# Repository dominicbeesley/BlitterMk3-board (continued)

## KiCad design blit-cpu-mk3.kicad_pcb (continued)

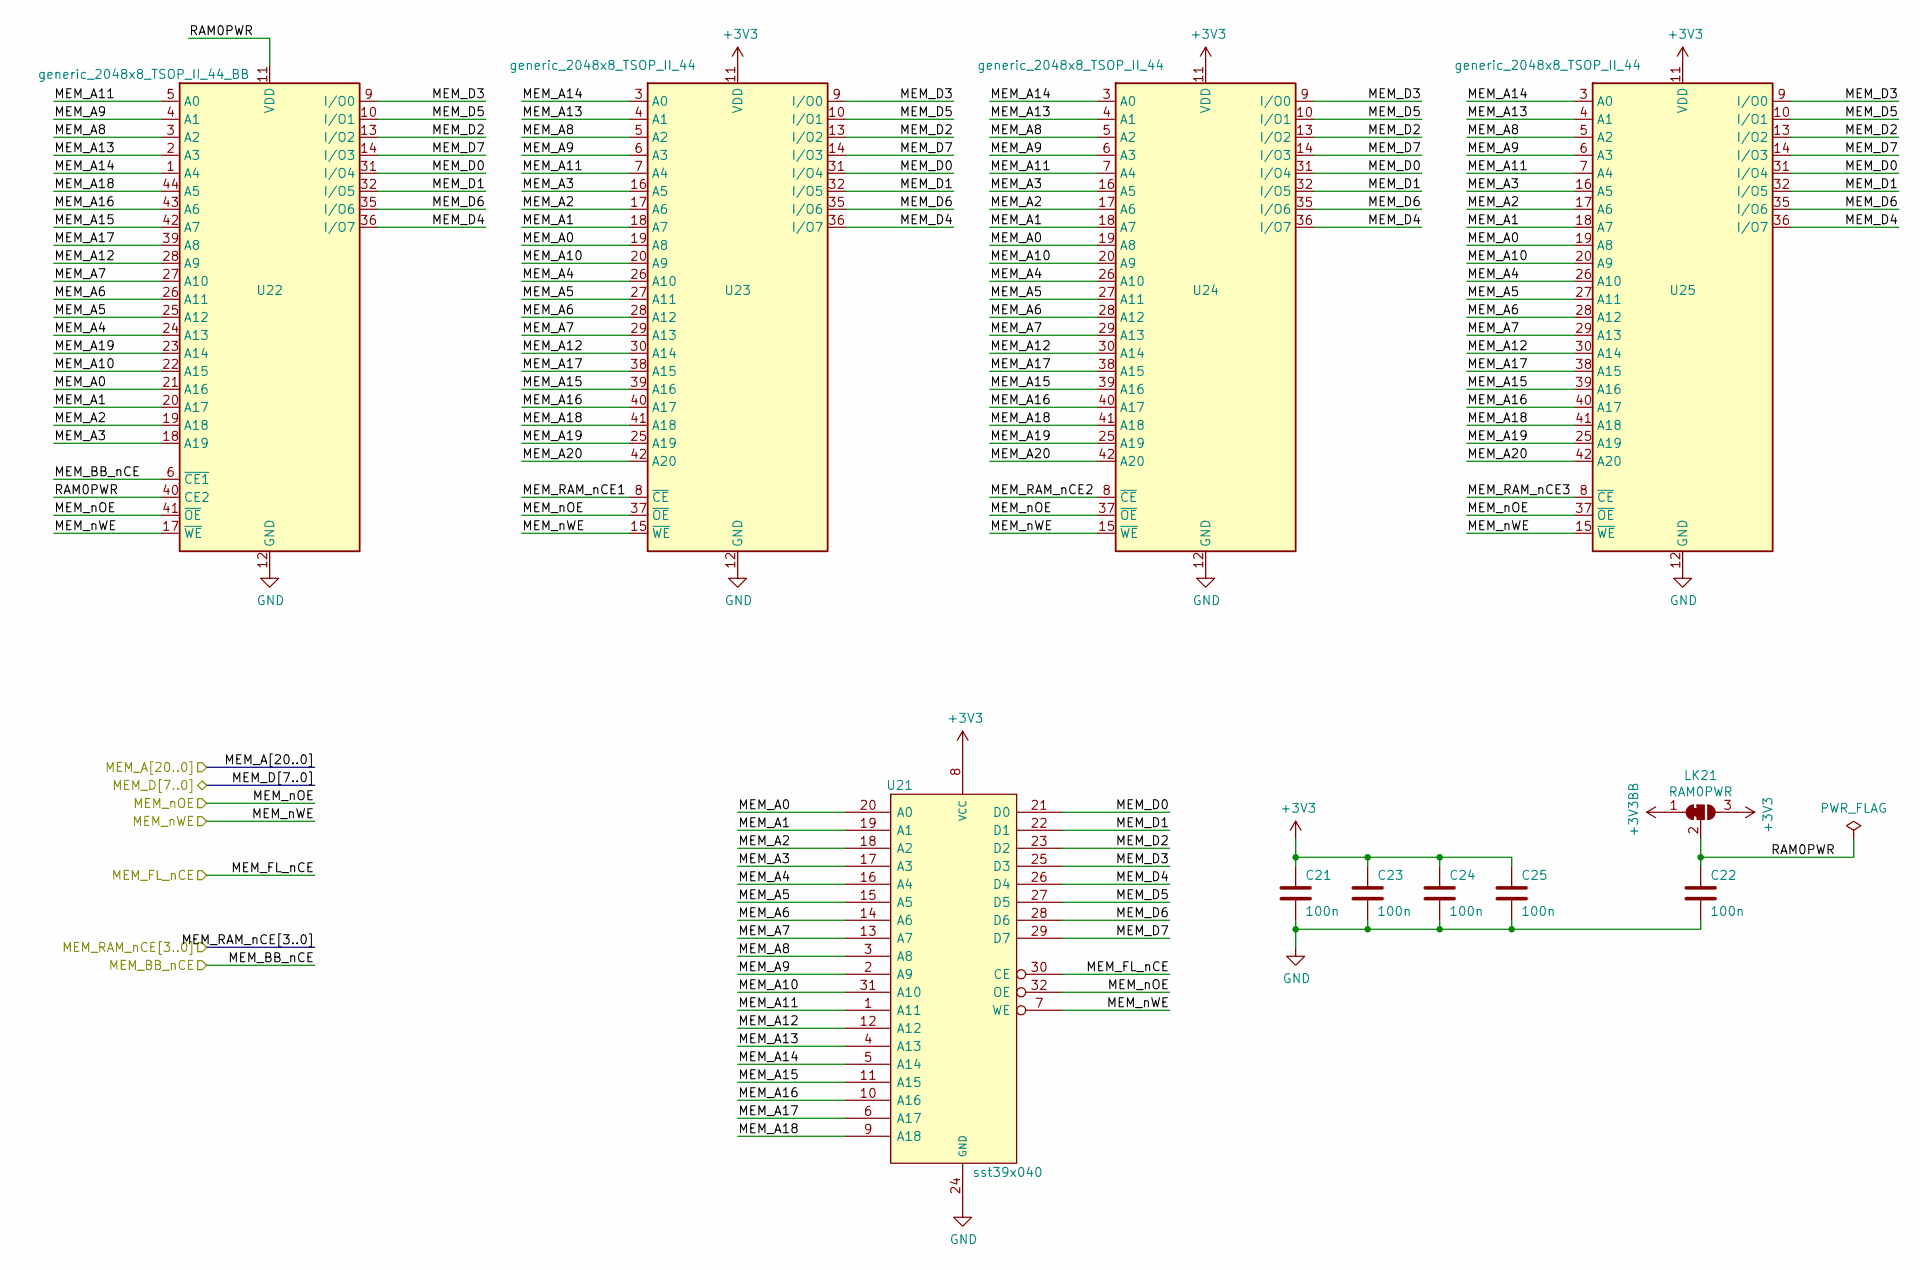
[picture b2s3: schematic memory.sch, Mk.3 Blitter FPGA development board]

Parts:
C21, C22, C23, C24, C25: 100n; C_0805
LK21: RAM0PWR; SolderJumper-3_P1.3mm_Bridged12_RoundedPad1.0x1.5mm
U21: sst39x040; TSOP-F-32_14x8mm_Pitch0.5mm
U22: generic_2048x8_TSOP_II_44_BB; TSOP-II-44_10.16x18.41mm_P0.8mm
U23, U24, U25: generic_2048x8_TSOP_II_44; TSOP-II-44_10.16x18.41mm_P0.8mm

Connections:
+3V3: C21.1, C23.1, C24.1, C25.1, LK21.3 (B), U21.8 (VCC), U23.11 (VDD), U23.33 (VDD), U24.11 (VDD), U24.33 (VDD), U25.11 (VDD), U25.33 (VDD); also elsewhere on the board
+3V3BB: LK21.1 (A); also elsewhere on the board
/MEM_BB_nCE_BB: U22.6 (~CE1); also elsewhere on the board
/MEM_FL_nCE: U21.30 (CE); also elsewhere on the board
/MEM_nOE: U21.32 (OE), U22.41 (~OE), U23.37 (~OE), U24.37 (~OE), U25.37 (~OE); also elsewhere on the board
/MEM_nWE: U21.7 (WE), U22.17 (~WE), U23.15 (~WE), U24.15 (~WE), U25.15 (~WE); also elsewhere on the board
/memory/MEM_A0: U21.20 (A0), U22.21 (A16), U23.19 (A8), U24.19 (A8), U25.19 (A8); also elsewhere on the board
/memory/MEM_A1: U21.19 (A1), U22.20 (A17), U23.18 (A7), U24.18 (A7), U25.18 (A7); also elsewhere on the board
/memory/MEM_A2: U21.18 (A2), U22.19 (A18), U23.17 (A6), U24.17 (A6), U25.17 (A6); also elsewhere on the board
/memory/MEM_A3: U21.17 (A3), U22.18 (A19), U23.16 (A5), U24.16 (A5), U25.16 (A5); also elsewhere on the board
/memory/MEM_A4: U21.16 (A4), U22.24 (A13), U23.26 (A10), U24.26 (A10), U25.26 (A10); also elsewhere on the board
/memory/MEM_A5: U21.15 (A5), U22.25 (A12), U23.27 (A11), U24.27 (A11), U25.27 (A11); also elsewhere on the board
/memory/MEM_A6: U21.14 (A6), U22.26 (A11), U23.28 (A12), U24.28 (A12), U25.28 (A12); also elsewhere on the board
/memory/MEM_A7: U21.13 (A7), U22.27 (A10), U23.29 (A13), U24.29 (A13), U25.29 (A13); also elsewhere on the board
/memory/MEM_A8: U21.3 (A8), U22.3 (A2), U23.5 (A2), U24.5 (A2), U25.5 (A2); also elsewhere on the board
/memory/MEM_A9: U21.2 (A9), U22.4 (A1), U23.6 (A3), U24.6 (A3), U25.6 (A3); also elsewhere on the board
/memory/MEM_A10: U21.31 (A10), U22.22 (A15), U23.20 (A9), U24.20 (A9), U25.20 (A9); also elsewhere on the board
/memory/MEM_A11: U21.1 (A11), U22.5 (A0), U23.7 (A4), U24.7 (A4), U25.7 (A4); also elsewhere on the board
/memory/MEM_A12: U21.12 (A12), U22.28 (A9), U23.30 (A14), U24.30 (A14), U25.30 (A14); also elsewhere on the board
/memory/MEM_A13: U21.4 (A13), U22.2 (A3), U23.4 (A1), U24.4 (A1), U25.4 (A1); also elsewhere on the board
/memory/MEM_A14: U21.5 (A14), U22.1 (A4), U23.3 (A0), U24.3 (A0), U25.3 (A0); also elsewhere on the board
/memory/MEM_A15: U21.11 (A15), U22.42 (A7), U23.39 (A16), U24.39 (A16), U25.39 (A16); also elsewhere on the board
/memory/MEM_A16: U21.10 (A16), U22.43 (A6), U23.40 (A17), U24.40 (A17), U25.40 (A17); also elsewhere on the board
/memory/MEM_A17: U21.6 (A17), U22.39 (A8), U23.38 (A15), U24.38 (A15), U25.38 (A15); also elsewhere on the board
/memory/MEM_A18: U21.9 (A18), U22.44 (A5), U23.41 (A18), U24.41 (A18), U25.41 (A18); also elsewhere on the board
/memory/MEM_A19: U22.23 (A14), U23.25 (A19), U24.25 (A19), U25.25 (A19); also elsewhere on the board
/memory/MEM_A20: U23.42 (A20), U24.42 (A20), U25.42 (A20); also elsewhere on the board
/memory/MEM_D0: U21.21 (D0), U22.31 (I/O4), U23.31 (I/O4), U24.31 (I/O4), U25.31 (I/O4); also elsewhere on the board
/memory/MEM_D1: U21.22 (D1), U22.32 (I/O5), U23.32 (I/O5), U24.32 (I/O5), U25.32 (I/O5); also elsewhere on the board
/memory/MEM_D2: U21.23 (D2), U22.13 (I/O2), U23.13 (I/O2), U24.13 (I/O2), U25.13 (I/O2); also elsewhere on the board
/memory/MEM_D3: U21.25 (D3), U22.9 (I/O0), U23.9 (I/O0), U24.9 (I/O0), U25.9 (I/O0); also elsewhere on the board
/memory/MEM_D4: U21.26 (D4), U22.36 (I/O7), U23.36 (I/O7), U24.36 (I/O7), U25.36 (I/O7); also elsewhere on the board
/memory/MEM_D5: U21.27 (D5), U22.10 (I/O1), U23.10 (I/O1), U24.10 (I/O1), U25.10 (I/O1); also elsewhere on the board
/memory/MEM_D6: U21.28 (D6), U22.35 (I/O6), U23.35 (I/O6), U24.35 (I/O6), U25.35 (I/O6); also elsewhere on the board
/memory/MEM_D7: U21.29 (D7), U22.14 (I/O3), U23.14 (I/O3), U24.14 (I/O3), U25.14 (I/O3); also elsewhere on the board
/memory/MEM_RAM_nCE1: U23.8 (~CE); also elsewhere on the board
/memory/MEM_RAM_nCE2: U24.8 (~CE); also elsewhere on the board
/memory/MEM_RAM_nCE3: U25.8 (~CE); also elsewhere on the board
/memory/RAM0PWR: C22.1, LK21.2 (C), U22.11 (VDD), U22.33 (VDD), U22.40 (CE2)

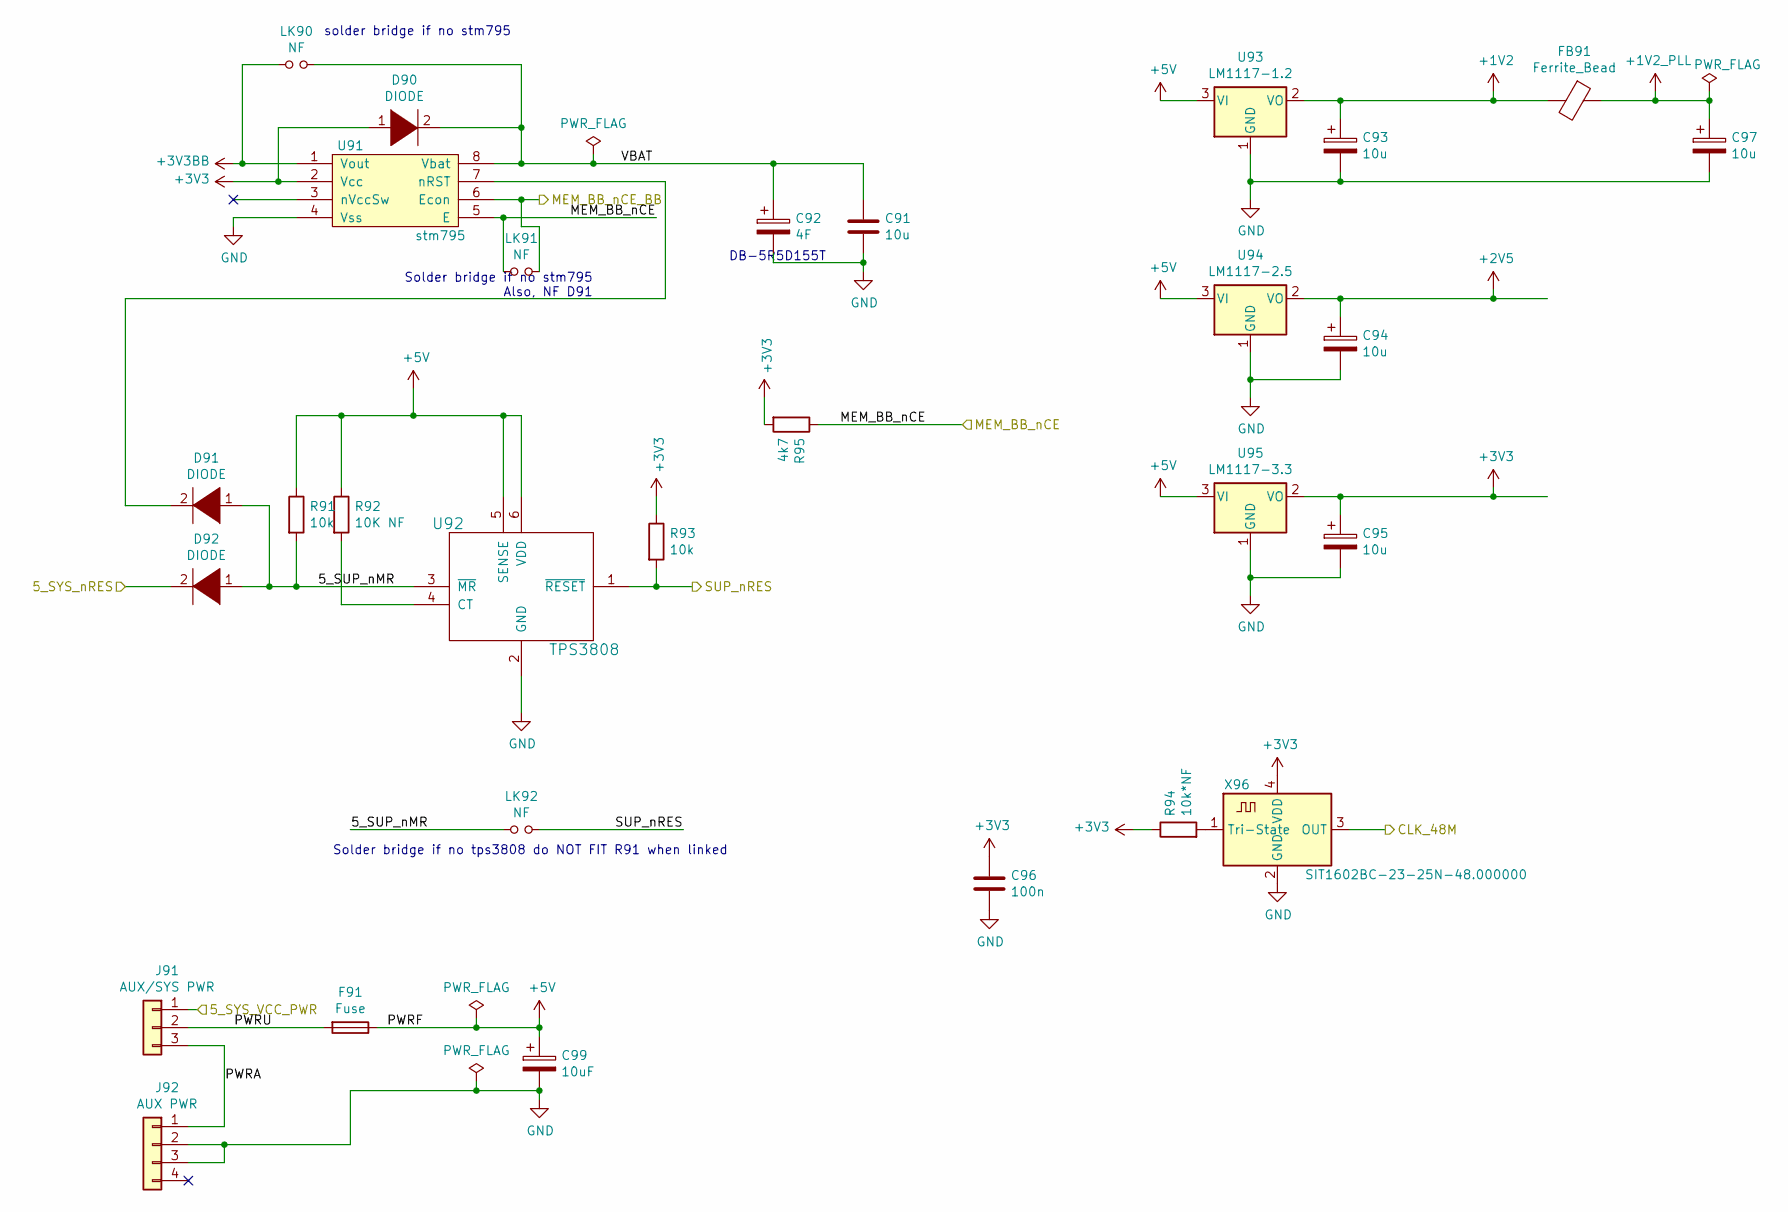
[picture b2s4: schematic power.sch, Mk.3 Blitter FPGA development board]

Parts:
C91, C93, C94, C95, C97: 10u; C_0805
C92: 4F; CP_Radial_D21.5mm_P5.00mmP11.5mm
C96: 100n; C_0805
C99: 10uF; C_0805
D90, D91, D92: DIODE; D_SOT-23_BAT54
F91: Fuse; R_1812
FB91: Ferrite_Bead; R_0402
J91: AUX/SYS PWR; PinHeader_1x03_P2.54mm_Vertical
J92: AUX PWR; Molex_KK-6410-04_04x2.54mm_Straight
LK90, LK91, LK92: NF; SolderJumper-2_P1.3mm_Open_RoundedPad1.0x1.5mm-domsmallctyd
R91, R93: 10k; R_0805
R92: 10K NF; R_0805
R94: 10k*NF; R_0805
R95: 4k7; R_0805
U91: stm795; SOIC-8_3.9x4.9mm_Pitch1.27mm
U92: TPS3808; SOT-23-6
U93: LM1117-1.2; SOT-223-3_TabPin2
U94: LM1117-2.5; SOT-223-3_TabPin2
U95: LM1117-3.3; SOT-223-3_TabPin2
X96: SIT1602BC-23-25N-48.000000; Oscillator_SMD_SiT1602-4pin_3.2x2.5mm

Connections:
+1V2: C93.1, FB91.2, U93.2 (VO); also elsewhere on the board
+1V2_PLL: C97.1, FB91.1; also elsewhere on the board
+2V5: C94.1, U94.2 (VO); also elsewhere on the board
+3V3: C95.1, C96.1, D90.1 (K), R93.1, R94.1, R95.2, U91.2 (Vcc), U95.2 (VO), X96.4 (VDD); also elsewhere on the board
+3V3BB: LK90.1, U91.1 (Vout); also elsewhere on the board
+5V: C99.1, F91.1, R91.1, R92.1, U92.5 (SENSE), U92.6 (VDD), U93.3 (VI), U94.3 (VI), U95.3 (VI); also elsewhere on the board
/5_SYS_VCC_PWR: J91.1; also elsewhere on the board
/5_SYS_nRES: D92.2 (A); also elsewhere on the board
/CLK_48M: X96.3 (OUT); also elsewhere on the board
/MEM_BB_nCE_BB: LK91.2, U91.6 (Econ); also elsewhere on the board
/MEM_RAM_nCE0: LK91.1, R95.1, U91.5 (E); also elsewhere on the board
/SUP_nRES: LK92.2, R93.2, U92.1 (~RESET); also elsewhere on the board
/power/5_SUP_nMR: D91.1 (K), D92.1 (K), LK92.1, R91.2, U92.3 (~MR)
/power/PWRA: J91.3, J92.1
/power/PWRU: F91.2, J91.2
/power/VBAT: C91.1, C92.1, D90.2 (A), LK90.2, U91.8 (Vbat)
unnamed: D91.2 (A), U91.7 (nRST)
unnamed: R92.2, U92.4 (CT)
unnamed: R94.2, X96.1 (Tri-State)

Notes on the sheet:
Solder bridge if no stm795 Also, NF D91
Solder bridge if no tps3808 do NOT FIT R91 when linked
DB-5R5D155T
solder bridge if no stm795

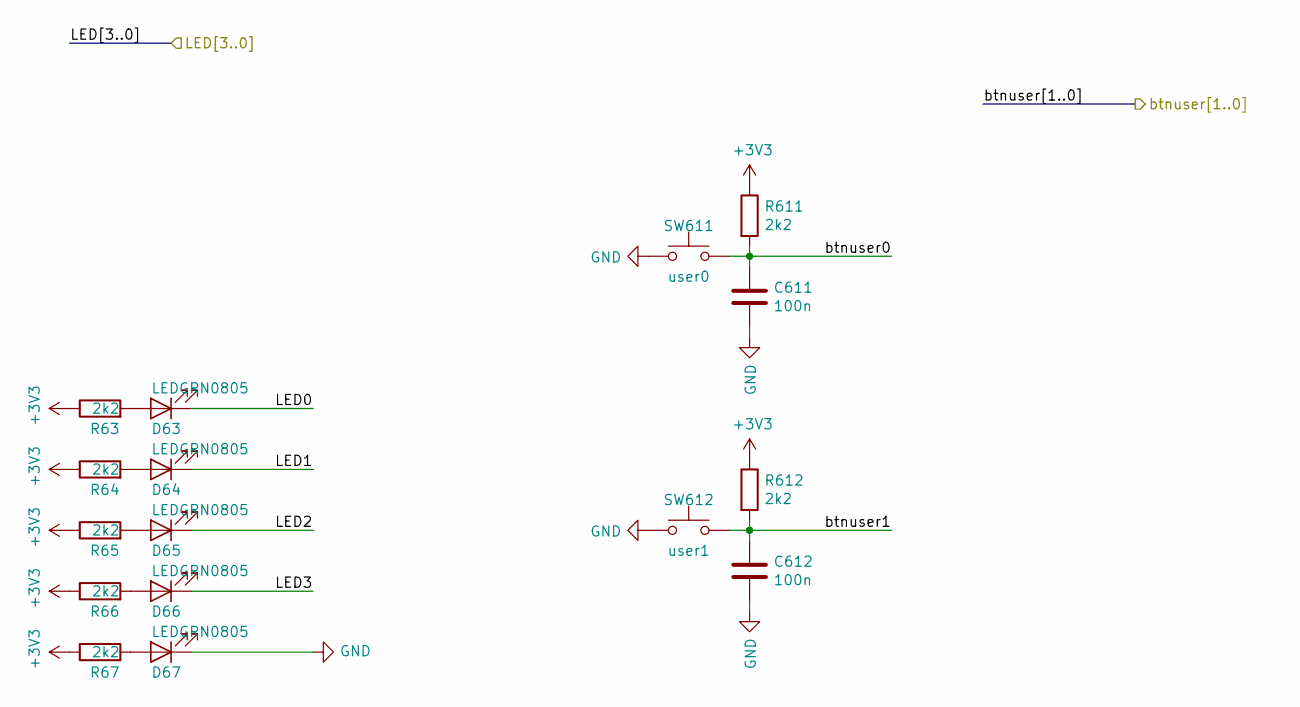
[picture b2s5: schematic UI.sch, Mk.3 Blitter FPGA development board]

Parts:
C611, C612: 100n; C_0805
D63, D64, D65, D66, D67: LEDGRN0805; LED_0805
R63, R64, R65, R66, R67, R611, R612: 2k2; R_0805
SW611: user0; SW_SPST_GEN
SW612: user1; SW_SPST_GEN

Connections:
+3V3: R63.1, R64.1, R65.1, R66.1, R67.1, R611.1, R612.1; also elsewhere on the board
/UI/LED0: D63.1 (K); also elsewhere on the board
/UI/LED1: D64.1 (K); also elsewhere on the board
/UI/LED2: D65.1 (K); also elsewhere on the board
/UI/LED3: D66.1 (K); also elsewhere on the board
/fpga_top/BTNUSER_i_0: C611.1, R611.2, SW611.1; also elsewhere on the board
/fpga_top/BTNUSER_i_1: C612.1, R612.2, SW612.1; also elsewhere on the board
unnamed: D63.2 (A), R63.2
unnamed: D64.2 (A), R64.2
unnamed: D65.2 (A), R65.2
unnamed: D66.2 (A), R66.2
unnamed: D67.2 (A), R67.2

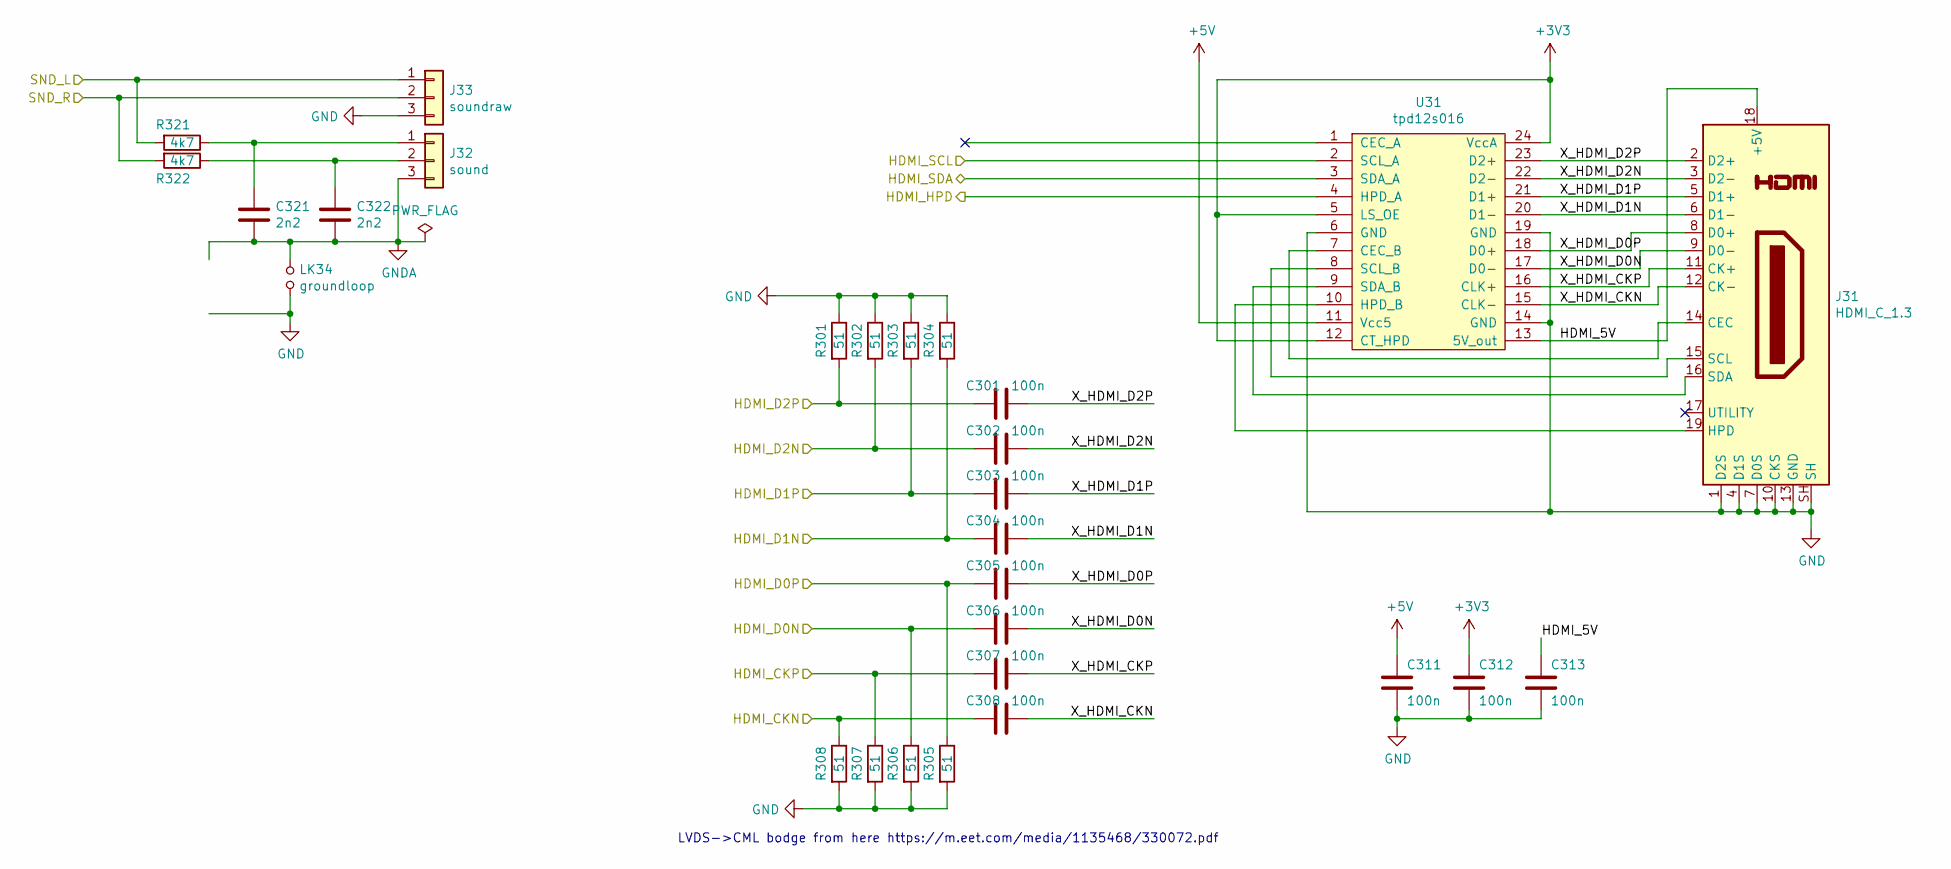
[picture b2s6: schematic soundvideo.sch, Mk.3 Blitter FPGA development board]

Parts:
C301, C302, C303, C304, C305, C306, C307, C308: 100n; C_0402
C311, C312, C313: 100n; C_0805
C321, C322: 2n2; C_0805
J31: HDMI_C_1.3; HDMI_Mini_Female_2001-1-2-21-00-BK-round-holes
J32: sound; PinHeader_1x03_P2.54mm_Vertical
J33: soundraw; PinHeader_1x03_P2.54mm_Vertical
LK34: groundloop; SolderJumper-2_P1.3mm_Open_RoundedPad1.0x1.5mm-domsmallctyd
R301, R302, R303, R304, R305, R306, R307, R308: 51; R_0402
R321, R322: 4k7; R_0805
U31: tpd12s016; TSSOP-24_4.4x7.8mm_Pitch0.65mm

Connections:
+3V3: C312.1, U31.5 (LS_OE), U31.12 (CT_HPD), U31.24 (VccA); also elsewhere on the board
+5V: C311.1, U31.11 (Vcc5); also elsewhere on the board
/HDMI_CKN: C308.2, R308.1; also elsewhere on the board
/HDMI_CKP: C307.2, R307.1; also elsewhere on the board
/HDMI_D0N: C306.2, R306.1; also elsewhere on the board
/HDMI_D0P: C305.2, R305.1; also elsewhere on the board
/HDMI_D1N: C304.2, R304.2; also elsewhere on the board
/HDMI_D1P: C303.2, R303.2; also elsewhere on the board
/HDMI_D2N: C302.2, R302.2; also elsewhere on the board
/HDMI_D2P: C301.2, R301.2; also elsewhere on the board
/HDMI_HPD: U31.4 (HPD_A); also elsewhere on the board
/HDMI_SCL: U31.2 (SCL_A); also elsewhere on the board
/HDMI_SDA: U31.3 (SDA_A); also elsewhere on the board
/SND_L: J33.1, R321.2; also elsewhere on the board
/SND_R: J33.2, R322.2; also elsewhere on the board
/soundvideo/HDMI_5V: C313.1, J31.18 (+5V), U31.13 (5V_out)
/soundvideo/X_HDMI_CKN: C308.1, J31.12 (CK-), U31.15 (CLK-)
/soundvideo/X_HDMI_CKP: C307.1, J31.11 (CK+), U31.16 (CLK+)
/soundvideo/X_HDMI_D0N: C306.1, J31.9 (D0-), U31.17 (D0-)
/soundvideo/X_HDMI_D0P: C305.1, J31.8 (D0+), U31.18 (D0+)
/soundvideo/X_HDMI_D1N: C304.1, J31.6 (D1-), U31.20 (D1-)
/soundvideo/X_HDMI_D1P: C303.1, J31.5 (D1+), U31.21 (D1+)
/soundvideo/X_HDMI_D2N: C302.1, J31.3 (D2-), U31.22 (D2-)
/soundvideo/X_HDMI_D2P: C301.1, J31.2 (D2+), U31.23 (D2+)
GNDA: C321.2, C322.2, J32.3, LK34.1
unnamed: C321.1, J32.1, R321.1
unnamed: C322.1, J32.2, R322.1
unnamed: J31.14 (CEC), U31.7 (CEC_B)
unnamed: J31.15 (SCL), U31.8 (SCL_B)
unnamed: J31.16 (SDA), U31.9 (SDA_B)
unnamed: J31.19 (HPD), U31.10 (HPD_B)

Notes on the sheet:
LVDS->CML bodge from here https://m.eet.com/media/1135468/330072.pdf

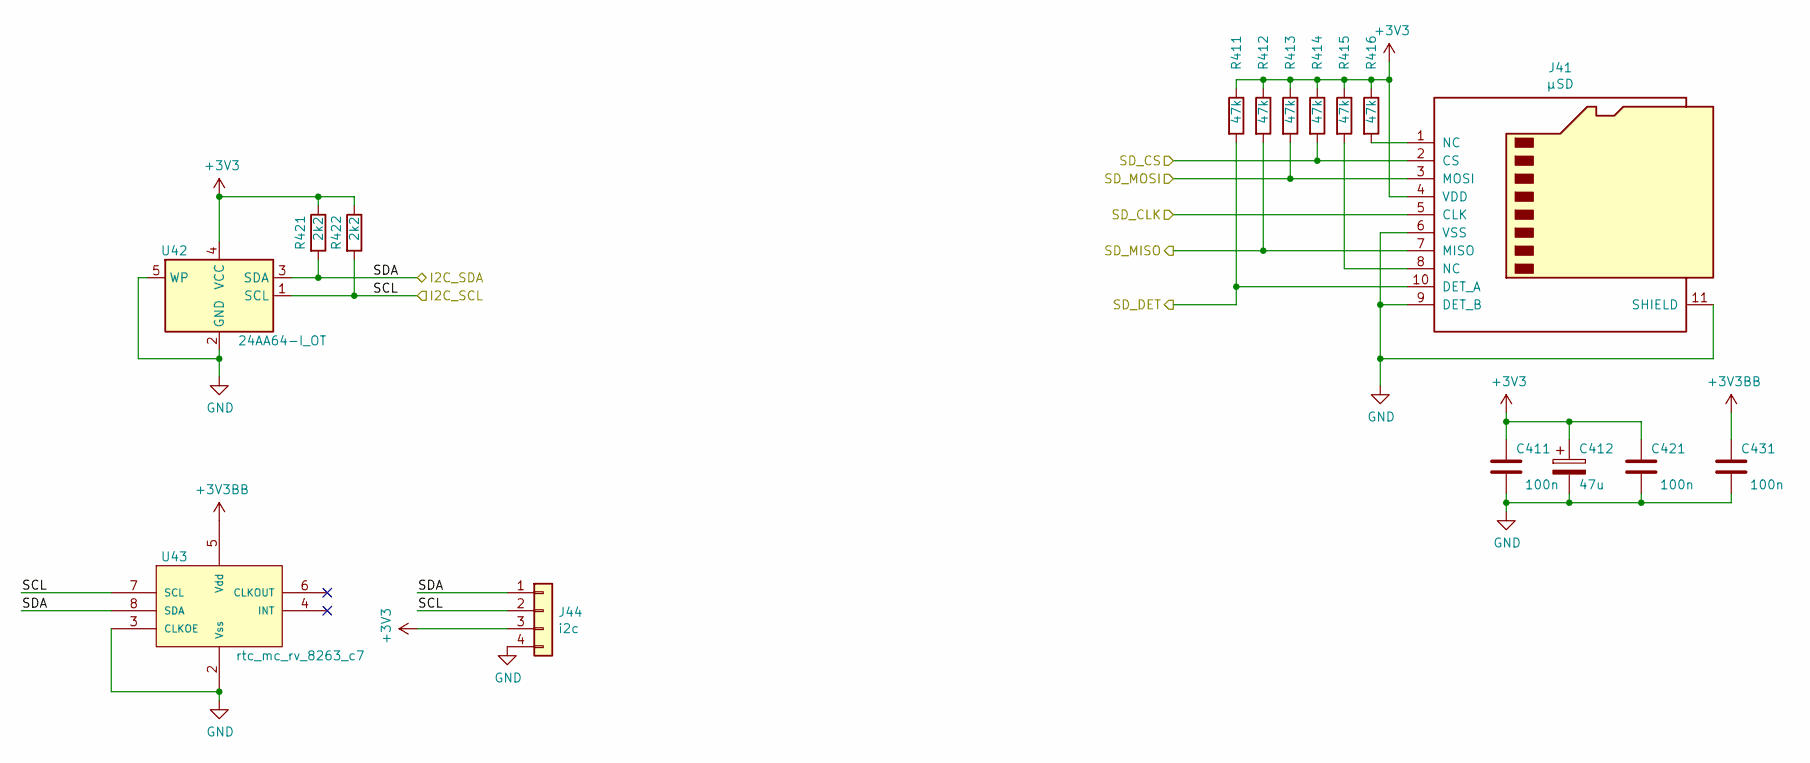
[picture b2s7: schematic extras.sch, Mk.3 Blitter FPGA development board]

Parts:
C411, C421, C431: 100n; C_0805
C412: 47u; C_0805
J41: μSD; hirose_micro_sd_card_socket
J44: i2c; PinHeader_1x04_P2.54mm_Vertical
R411, R412, R413, R414, R415, R416: 47k; R_0805
R421, R422: 2k2; R_0805
U42: 24AA64-I_OT; SOT-23-5
U43: rtc_mc_rv_8263_c7; 8pin_mini_rtc

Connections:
+3V3: C411.1, C412.1, C421.1, J41.4 (VDD), J44.3, R411.1, R412.1, R413.1, R414.1, R415.1, R416.1, R421.1, R422.1, U42.4 (VCC); also elsewhere on the board
+3V3BB: C431.1, U43.5 (Vdd); also elsewhere on the board
/I2C_SCL: J44.2, R422.2, U42.1 (SCL), U43.7 (SCL); also elsewhere on the board
/I2C_SDA: J44.1, R421.2, U42.3 (SDA), U43.8 (SDA); also elsewhere on the board
/SD_CLK: J41.5 (CLK); also elsewhere on the board
/SD_CS: J41.2 (CS), R414.2; also elsewhere on the board
/SD_DET: J41.10 (DET_A), R411.2; also elsewhere on the board
/SD_MISO: J41.7 (MISO), R412.2; also elsewhere on the board
/SD_MOSI: J41.3 (MOSI), R413.2; also elsewhere on the board
unnamed: J41.1 (NC), R416.2
unnamed: J41.8 (NC), R415.2

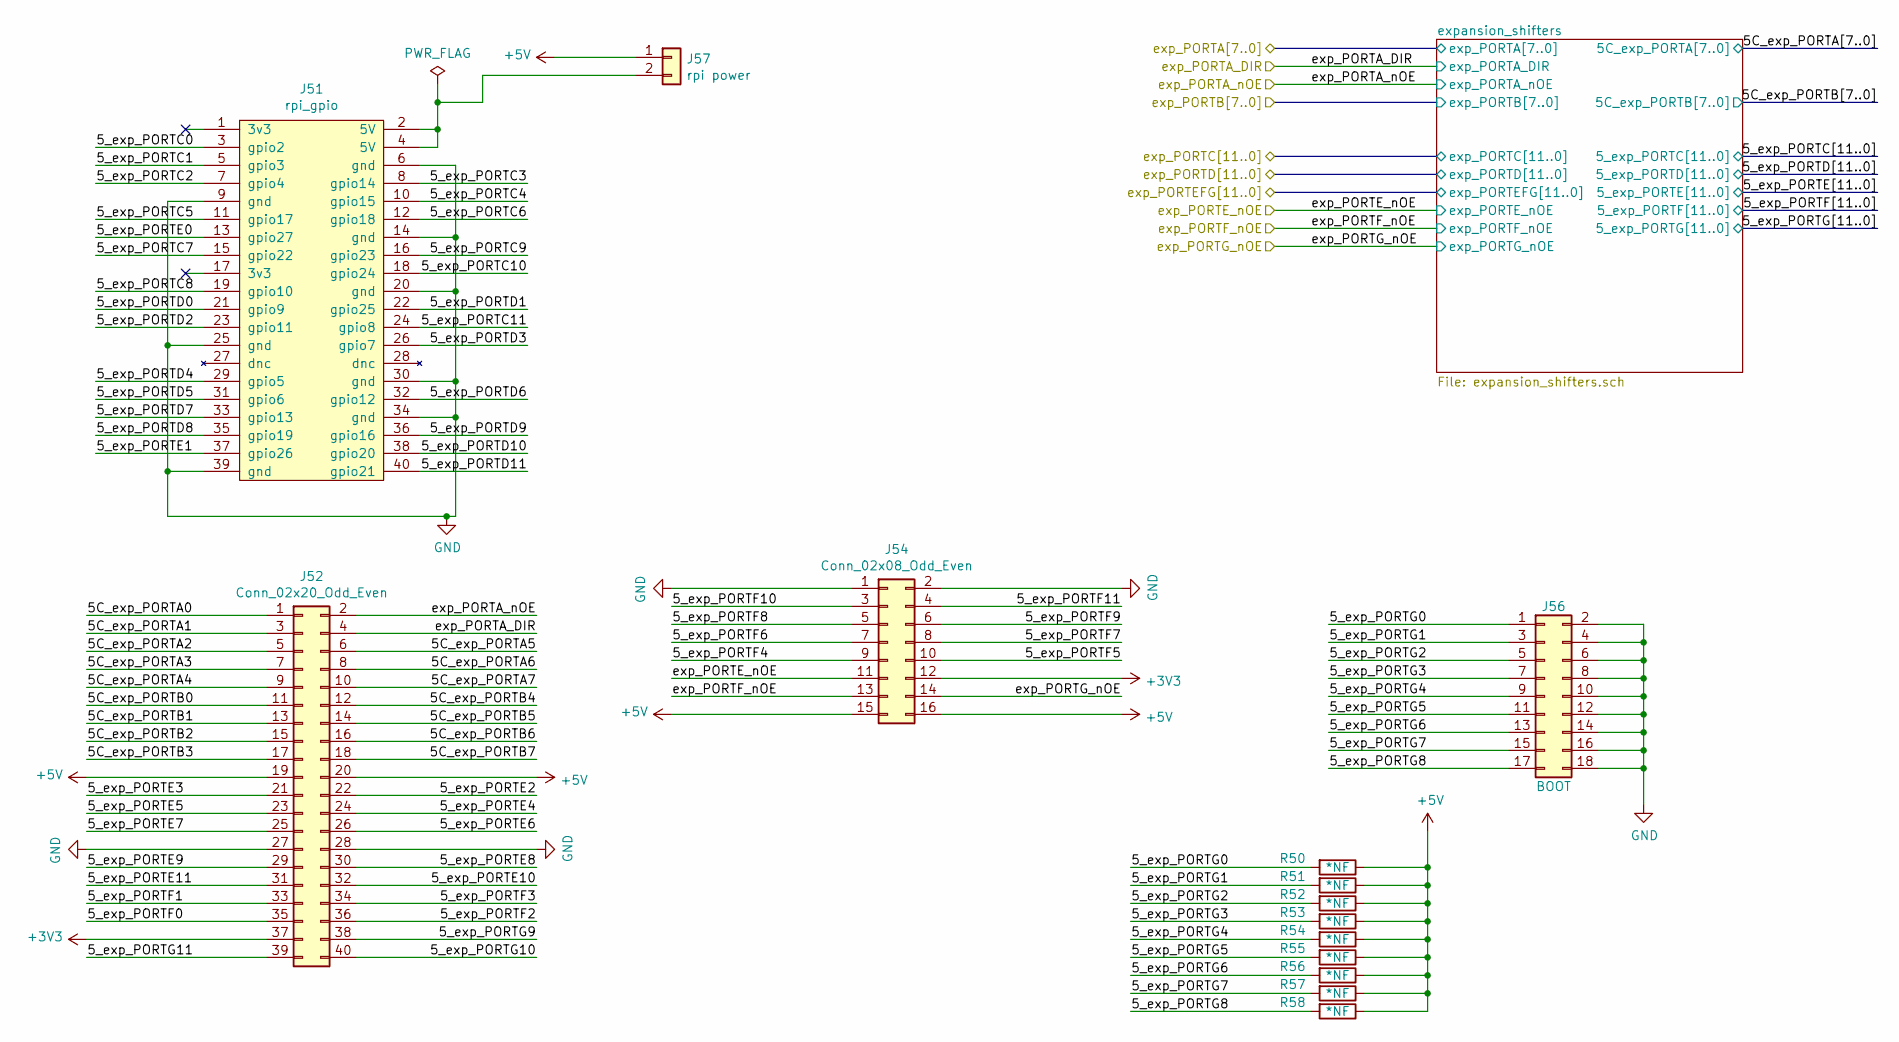
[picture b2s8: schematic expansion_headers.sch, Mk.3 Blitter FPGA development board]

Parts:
J51: rpi_gpio; PinSocket_2x20_P2.54mm_Vertical_SMD-dom
J52: Conn_02x20_Odd_Even; PinHeader_2x20_P2.54mm_Vertical_SMD-dom
J54: Conn_02x08_Odd_Even; PinHeader_2x08_P2.54mm_Vertical_SMD-dom
J56: BOOT; PinHeader_2x09_P2.54mm_Vertical
J57: rpi power; PinHeader_1x02_P2.54mm_Vertical
R50, R51, R52, R53, R54, R55, R56, R57, R58: *NF; R_0805

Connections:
+3V3: J52.37, J54.12; also elsewhere on the board
+5V: J52.19, J52.20, J54.15, J54.16, J57.1, R50.1, R51.1, R52.1, R53.1, R54.1, R55.1, R56.1, R57.1, R58.1; also elsewhere on the board
/exp_PORTA_DIR: J52.4; also elsewhere on the board
/exp_PORTA_nOE: J52.2; also elsewhere on the board
/exp_PORTE_nOE: J54.11; also elsewhere on the board
/exp_PORTF_nOE: J54.13; also elsewhere on the board
/exp_PORTG_nOE: J54.14; also elsewhere on the board
/expansion_headers/5C_exp_PORTA0: J52.1; also elsewhere on the board
/expansion_headers/5C_exp_PORTA1: J52.3; also elsewhere on the board
/expansion_headers/5C_exp_PORTA2: J52.5; also elsewhere on the board
/expansion_headers/5C_exp_PORTA3: J52.7; also elsewhere on the board
/expansion_headers/5C_exp_PORTA4: J52.9; also elsewhere on the board
/expansion_headers/5C_exp_PORTA5: J52.6; also elsewhere on the board
/expansion_headers/5C_exp_PORTA6: J52.8; also elsewhere on the board
/expansion_headers/5C_exp_PORTA7: J52.10; also elsewhere on the board
/expansion_headers/5C_exp_PORTB0: J52.11; also elsewhere on the board
/expansion_headers/5C_exp_PORTB1: J52.13; also elsewhere on the board
/expansion_headers/5C_exp_PORTB2: J52.15; also elsewhere on the board
/expansion_headers/5C_exp_PORTB3: J52.17; also elsewhere on the board
/expansion_headers/5C_exp_PORTB4: J52.12; also elsewhere on the board
/expansion_headers/5C_exp_PORTB5: J52.14; also elsewhere on the board
/expansion_headers/5C_exp_PORTB6: J52.16; also elsewhere on the board
/expansion_headers/5C_exp_PORTB7: J52.18; also elsewhere on the board
/expansion_headers/5_exp_PORTC0: J51.3 (gpio2); also elsewhere on the board
/expansion_headers/5_exp_PORTC1: J51.5 (gpio3); also elsewhere on the board
/expansion_headers/5_exp_PORTC2: J51.7 (gpio4); also elsewhere on the board
/expansion_headers/5_exp_PORTC3: J51.8 (gpio14); also elsewhere on the board
/expansion_headers/5_exp_PORTC4: J51.10 (gpio15); also elsewhere on the board
/expansion_headers/5_exp_PORTC5: J51.11 (gpio17); also elsewhere on the board
/expansion_headers/5_exp_PORTC6: J51.12 (gpio18); also elsewhere on the board
/expansion_headers/5_exp_PORTC7: J51.15 (gpio22); also elsewhere on the board
/expansion_headers/5_exp_PORTC8: J51.19 (gpio10); also elsewhere on the board
/expansion_headers/5_exp_PORTC9: J51.16 (gpio23); also elsewhere on the board
/expansion_headers/5_exp_PORTC10: J51.18 (gpio24); also elsewhere on the board
/expansion_headers/5_exp_PORTC11: J51.24 (gpio8); also elsewhere on the board
/expansion_headers/5_exp_PORTD0: J51.21 (gpio9); also elsewhere on the board
/expansion_headers/5_exp_PORTD1: J51.22 (gpio25); also elsewhere on the board
/expansion_headers/5_exp_PORTD2: J51.23 (gpio11); also elsewhere on the board
/expansion_headers/5_exp_PORTD3: J51.26 (gpio7); also elsewhere on the board
/expansion_headers/5_exp_PORTD4: J51.29 (gpio5); also elsewhere on the board
/expansion_headers/5_exp_PORTD5: J51.31 (gpio6); also elsewhere on the board
/expansion_headers/5_exp_PORTD6: J51.32 (gpio12); also elsewhere on the board
/expansion_headers/5_exp_PORTD7: J51.33 (gpio13); also elsewhere on the board
/expansion_headers/5_exp_PORTD8: J51.35 (gpio19); also elsewhere on the board
/expansion_headers/5_exp_PORTD9: J51.36 (gpio16); also elsewhere on the board
/expansion_headers/5_exp_PORTD10: J51.38 (gpio20); also elsewhere on the board
/expansion_headers/5_exp_PORTD11: J51.40 (gpio21); also elsewhere on the board
/expansion_headers/5_exp_PORTE0: J51.13 (gpio27); also elsewhere on the board
/expansion_headers/5_exp_PORTE1: J51.37 (gpio26); also elsewhere on the board
/expansion_headers/5_exp_PORTE2: J52.22; also elsewhere on the board
/expansion_headers/5_exp_PORTE3: J52.21; also elsewhere on the board
/expansion_headers/5_exp_PORTE4: J52.24; also elsewhere on the board
/expansion_headers/5_exp_PORTE5: J52.23; also elsewhere on the board
/expansion_headers/5_exp_PORTE6: J52.26; also elsewhere on the board
/expansion_headers/5_exp_PORTE7: J52.25; also elsewhere on the board
/expansion_headers/5_exp_PORTE8: J52.30; also elsewhere on the board
/expansion_headers/5_exp_PORTE9: J52.29; also elsewhere on the board
/expansion_headers/5_exp_PORTE10: J52.32; also elsewhere on the board
/expansion_headers/5_exp_PORTE11: J52.31; also elsewhere on the board
/expansion_headers/5_exp_PORTF0: J52.35; also elsewhere on the board
/expansion_headers/5_exp_PORTF1: J52.33; also elsewhere on the board
/expansion_headers/5_exp_PORTF2: J52.36; also elsewhere on the board
/expansion_headers/5_exp_PORTF3: J52.34; also elsewhere on the board
/expansion_headers/5_exp_PORTF4: J54.9; also elsewhere on the board
/expansion_headers/5_exp_PORTF5: J54.10; also elsewhere on the board
/expansion_headers/5_exp_PORTF6: J54.7; also elsewhere on the board
/expansion_headers/5_exp_PORTF7: J54.8; also elsewhere on the board
/expansion_headers/5_exp_PORTF8: J54.5; also elsewhere on the board
/expansion_headers/5_exp_PORTF9: J54.6; also elsewhere on the board
/expansion_headers/5_exp_PORTF10: J54.3; also elsewhere on the board
/expansion_headers/5_exp_PORTF11: J54.4; also elsewhere on the board
/expansion_headers/5_exp_PORTG0: J56.1, R50.2; also elsewhere on the board
/expansion_headers/5_exp_PORTG1: J56.3, R51.2; also elsewhere on the board
/expansion_headers/5_exp_PORTG2: J56.5, R52.2; also elsewhere on the board
/expansion_headers/5_exp_PORTG3: J56.7, R53.2; also elsewhere on the board
/expansion_headers/5_exp_PORTG4: J56.9, R54.2; also elsewhere on the board
/expansion_headers/5_exp_PORTG5: J56.11, R55.2; also elsewhere on the board
/expansion_headers/5_exp_PORTG6: J56.13, R56.2; also elsewhere on the board
/expansion_headers/5_exp_PORTG7: J56.15, R57.2; also elsewhere on the board
/expansion_headers/5_exp_PORTG8: J56.17, R58.2; also elsewhere on the board
/expansion_headers/5_exp_PORTG9: J52.38; also elsewhere on the board
/expansion_headers/5_exp_PORTG10: J52.40; also elsewhere on the board
/expansion_headers/5_exp_PORTG11: J52.39; also elsewhere on the board
unnamed: J51.2 (5V), J51.4 (5V), J57.2

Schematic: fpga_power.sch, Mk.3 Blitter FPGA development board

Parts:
C81, C82, C83, C84, C85, C86, C87, C88, C89, C810, C811, C812, C814, C815: 100n; C_0402
J81: JTAG; IDC-Header_2x05_P2.54mm_Vertical
J82: Jumper; PinHeader_1x02_P2.54mm_Vertical
R81: 1k; R_0805
R82, R83, R84, R85, R86, R87: 10k; R_0805
SW81: nConfig; SW_SPST_GEN
U8: 10M16DCF256I7G_mk3pinstest; MAX10_FBGA_256_dom

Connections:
+1V2: C814.1, C815.1, U8.F6 (VCC), U8.G7 (VCC), U8.G9 (VCC), U8.H8 (VCC), U8.H9 (VCC), U8.H10 (VCC), U8.J7 (VCC), U8.J8 (VCC), U8.J9 (VCC), U8.K8 (VCC), U8.K10 (VCC); also elsewhere on the board
+1V2_PLL: C81.1, C82.1, C83.1, C84.1, U8.D4 (VCCD_PLL3), U8.D13 (VCCD_PLL2), U8.M5 (VCCD_PLL1), U8.N13 (VCCD_PLL4); also elsewhere on the board
+2V5: C85.1, C86.1, C87.1, C88.1, U8.D5 (VCCA3), U8.E4 (VCCA3), U8.E5 (VCCA3), U8.E12 (VCCA2), U8.L5 (VCCA1), U8.M12 (VCCA4), U8.N10 (VCCIO4), U8.N11 (VCCIO4); also elsewhere on the board
+3V3: C89.1, C810.1, C811.1, C812.1, J81.4, J82.2, R82.1, R83.1, R84.1, R85.1, R86.2, U8.C7 (VCCIO8), U8.D7 (VCCIO8), U8.D8 (VCCIO8), U8.D10 (VCCIO7), U8.D11 (VCCIO7), U8.F13 (VCCIO6), U8.G4 (VCCIO1A), U8.G13 (VCCIO6), U8.H4 (VCCIO1A), U8.H13 (VCCIO6), U8.J4 (VCCIO1B), U8.J13 (VCCIO6), U8.K4 (VCCIO2), U8.K13 (VCCIO5), U8.L4 (VCCIO2), U8.L13 (VCCIO5), U8.M13 (VCCIO5), U8.N6 (VCCIO3), U8.N7 (VCCIO3), U8.N8 (VCCIO3); also elsewhere on the board
/ALTERA_CONFIG_SEL: J82.1, R87.2; also elsewhere on the board
/ALTERA_CONF_DONE: R85.2; also elsewhere on the board
/ALTERA_nCONFIG: R86.1, SW81.1; also elsewhere on the board
/ALTERA_nSTATUS: R84.2; also elsewhere on the board
/fpga_power/~ALTERA_TCK~: J81.1, R81.2, U8.H3 (~ALTERA_TCK~)
/fpga_power/~ALTERA_TDI~: J81.9, R83.2, U8.G1 (~ALTERA_TDI~)
/fpga_power/~ALTERA_TDO~: J81.3, U8.H1 (~ALTERA_TDO~)
/fpga_power/~ALTERA_TMS~: J81.5, R82.2, U8.H2 (~ALTERA_TMS~)

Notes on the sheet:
1v2 DECOUPLERS!
